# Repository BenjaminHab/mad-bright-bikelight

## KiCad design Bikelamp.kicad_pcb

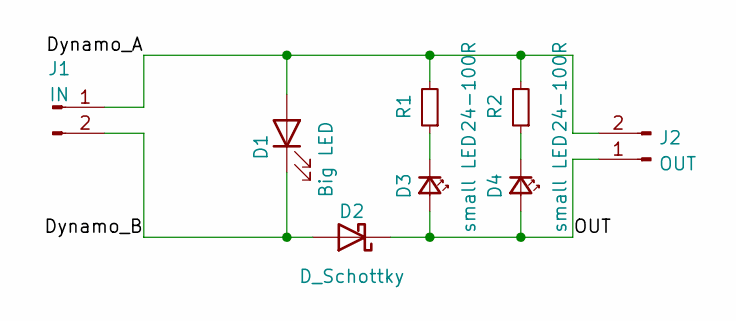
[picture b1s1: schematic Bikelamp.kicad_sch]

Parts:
D1: Big LED; Cree 5050; MPN JR5050BWT-K-B40EB0000-N0000001
D2: D_Schottky; D_SOD-123F; MPN PMEG3010EH,115
D3, D4: small LED; Cree 3030; MPN JK3030AWT-00-0000-000A0UJ465E
J1: IN; SolderWire-0.25sqmm_1x02_P4.5mm_D0.65mm_OD2mm_Relief
J2: OUT; SolderWire-0.25sqmm_1x02_P4.5mm_D0.65mm_OD2mm_Relief
R1, R2: 24-100R; R_0603_1608Metric_Pad0.98x0.95mm_HandSolder

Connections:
/Dynamo_A: D1.2 (A), J1.1, J2.2, R1.2, R2.2
/Dynamo_B: D1.1 (K), D2.2 (A), J1.2
/OUT: D2.1 (K), D3.2 (A), D4.2 (A), J2.1
unnamed: D3.1 (K), R1.1
unnamed: D4.1 (K), R2.1

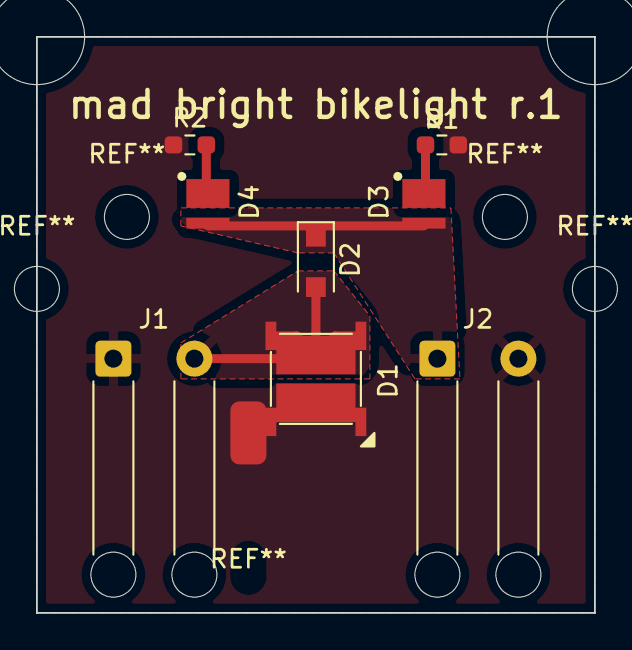
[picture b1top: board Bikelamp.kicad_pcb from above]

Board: 2 copper layers, 31.0 x 32.0 mm, 8 parts (0 on the bottom side), 5 nets.

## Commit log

2022-05-17 Initial version
